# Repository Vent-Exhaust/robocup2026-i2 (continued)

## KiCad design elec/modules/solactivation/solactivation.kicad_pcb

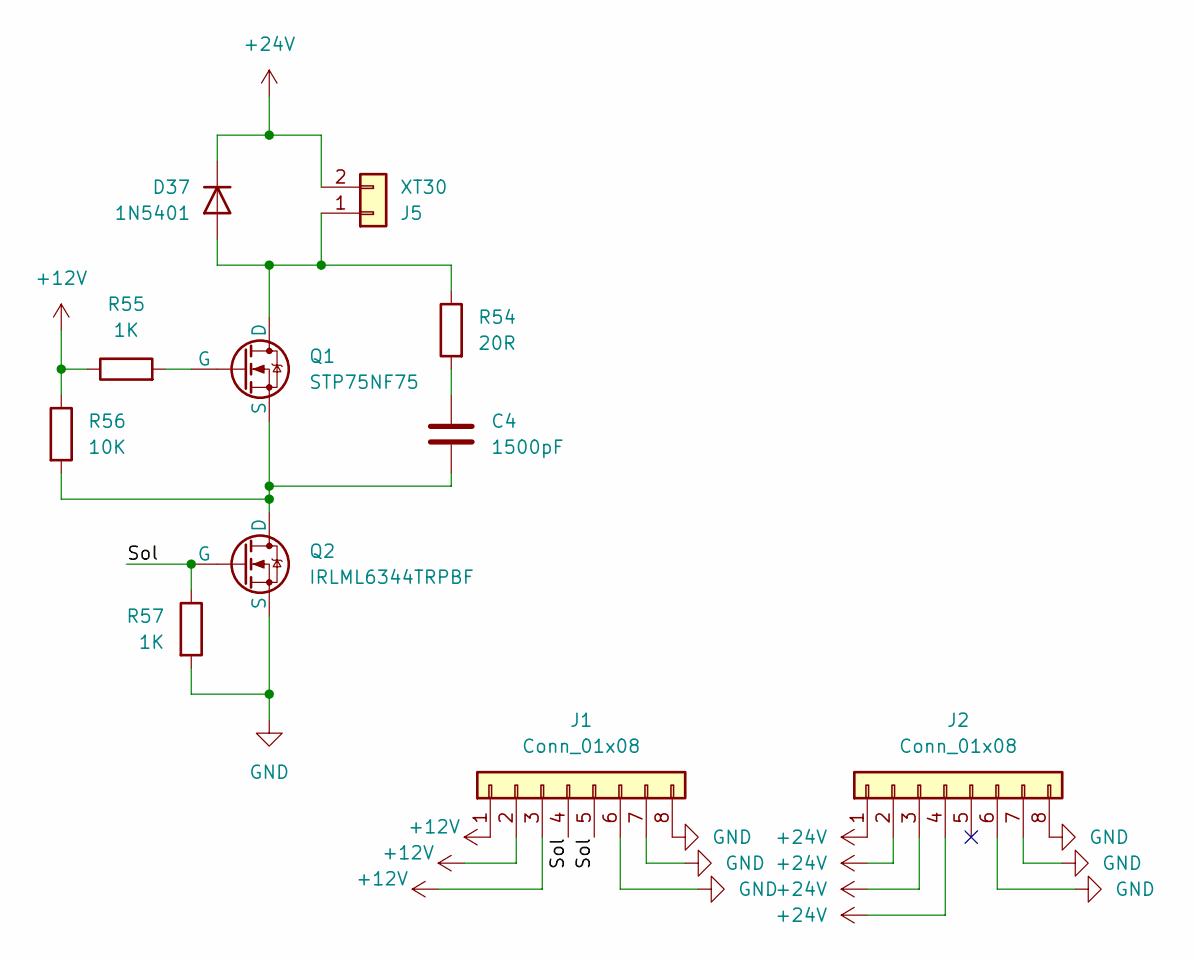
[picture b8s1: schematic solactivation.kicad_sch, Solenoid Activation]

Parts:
C4: 1500pF; cap0603; LCSC C107060
D37: 1N5401; D_DO-201AD_P15.24mm_Horizontal; LCSC C179506
J1, J2: Conn_01x08; PinSocket_1x08_P2.54mm_Vertical
J5: XT30; AMASS_XT30-F; LCSC C108769
Q1: STP75NF75; TO-220-3_Vertical; Mouser Part Number 726-IPD050N10N5ATMA1; LCSC C13678
Q2: IRLML6344TRPBF; SOT95P237X112-3N; Mouser Part Number 942-IRLML6344TRPBF
R54: 20R; res0603; LCSC C22950
R55, R57: 1K; res0603; LCSC C21190
R56: 10K; res0603; LCSC C25804

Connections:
+12V: J1.1, J1.2, J1.3, R55.1, R56.1
+24V: D37.1 (K), J2.1, J2.2, J2.3, J2.4, J5.2
/Sol: J1.4, J1.5, Q2.1 (G), R57.1
GND: J1.6, J1.7, J1.8, J2.6, J2.7, J2.8, Q2.2 (S), R57.2
unnamed: C4.1, R54.2
unnamed: D37.2 (A), J5.1, Q1.2 (D), R54.1
unnamed: Q1.1 (G), R55.2
unnamed: C4.2, Q1.3 (S), Q2.3 (D), R56.2

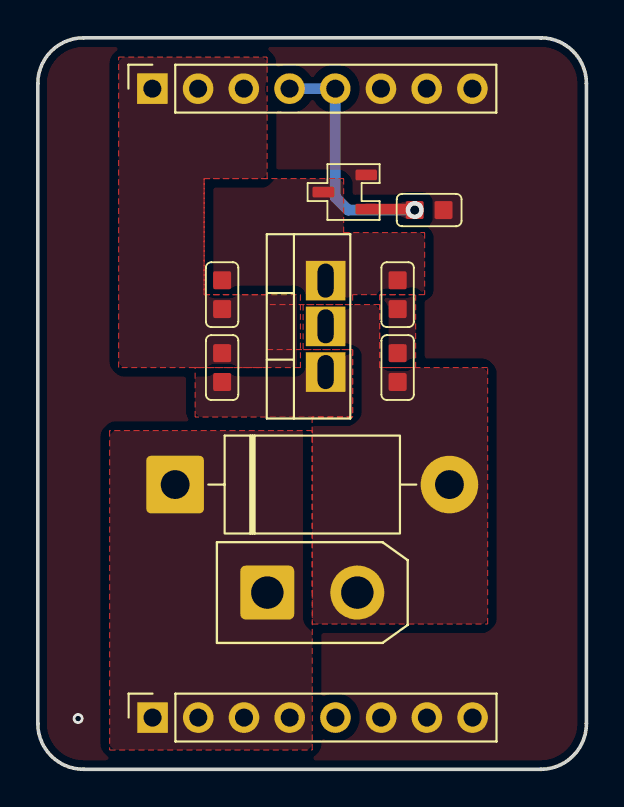
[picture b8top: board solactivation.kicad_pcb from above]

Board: 2 copper layers, 30.5 x 40.6 mm, 11 parts (0 on the bottom side), 8 nets.

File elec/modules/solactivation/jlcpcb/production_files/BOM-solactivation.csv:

Comment,Designator,Footprint,LCSC,Quantity
10K,R56,res0603,C25804,1
1500pF,C4,cap0603,C1595,1
1K,"R55,R57",res0603,C21190,2
20R,R54,res0603,C22950,1
IRLML6344TRPBF,Q2,SOT95P237X112-3N,,1

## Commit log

2025-10-08 added stuff
2025-10-14 did drivers yay
2025-10-14 did boost without caps for now might have to re config stitch vias pos
2025-10-14 fuction more impt!
2025-10-14 did motor driver example
2025-10-21 i think thats drivers done
2025-10-21 aligned pogos
2025-10-21 sleepy but did most pcbs
2025-10-21 updated modules dxfs
2025-10-21 motor drivers completed
2025-10-21 touched buck schematics
2025-10-22 added fusion fat module
2025-10-30 potentially did somethign
2025-10-31 moving somethings
2025-11-02 fix: edited buck
    moved a singular tantulum by a few mm
2025-11-02 did buck +3d models_ the actual buck er 3d mode'
2025-11-02 added TPS5430DDAG4 3d models
2025-11-03 finishe dcaps for boost
2025-11-03 did stuff
2025-11-03 forgot to close kicaed
2025-11-03 finished pcbs-silkscrfeen pcbs seem halal
2025-11-03 added teardrops and sus via
2025-11-03 added silkscreen
2025-11-05 did pcba for bucks
2025-11-05 did pcba for buck and boos5t
2025-11-30 added Bourns TC33X-2-104E
2025-11-30 feat: added pot to boost
2025-11-30 added 3d model for boost + PCBA
2025-11-30 Finished slaving avay buck done +PCBA
2025-11-30 added v1 to bucks
2025-11-30 added name cos why not
2025-12-02 chore: production files; chore: rev num for solactivation
2025-12-02 chore: boost production files
2025-12-02 chore: buck production files
2025-12-02 chore: boostcaps production files
2025-12-02 fix: boostcaps revision number; chore: boostcaps production files
2025-12-02 changed buck footprint
2025-12-10 feat: layer1-pcb-v1.0
2025-12-10 feat: cone mirror files
2025-12-10 partially did tofs
2026-01-02 Revert "Merge branch 'main' of https://github.com/2-chairs/robocup2026-i2"
    This reverts commit a28d608313404cc618c1ce11ffefa503b88e08b3, reversing
    changes made to 7cc45da3019f5272dff102d14f68ce9626e855f6.
2026-01-02 Revert "partially did tofs"
    This reverts commit 7cc45da3019f5272dff102d14f68ce9626e855f6.
2026-01-02 re buploaded tofs + kinda renamed and commited plagiarism
2026-01-03 made schematics more organised ish for tofs
    Hope i didnt mess anyuthingn up
2026-01-05 got l2 out of l2
2026-01-05 veryuseless change added dxf
2026-01-05 added light ring schematics
2026-01-05 closed kicad oops
2026-01-06 feat: light ring
2026-01-06 chore: update l1 dxf
2026-01-06 feat: layer1 light ring
2026-01-06 chore: stupid light ring more
2026-01-07 did l1 light ring partially
2026-01-07 done lightring
2026-01-07 added connectors for modules in schmatics
2026-01-07 mostly done with l1 scchematics
2026-01-08 fix: uploaded l1 2.0 dxf
2026-01-08 chore: src laser cutting files
2026-01-08 chore: wheels 3mf files
2026-01-08 chore: kicker 3mf files
2026-01-08 chore: dribbler 3mf files
2026-01-08 fix: dribbler 3mf files
2026-01-08 l1:added boost measurements
2026-01-08 feat: battery mount parts
2026-01-08 almost done maybe
2026-01-08 l1:connected most stuff
2026-01-08 fix: wheels cad
2026-01-08 styles: font
2026-01-08 fix: layer1 pcb
2026-01-09 feat: layer2 buck-module footprint and symbol
2026-01-09 feat: layer2 motor driver footprint and schematic
2026-01-09 feat: did something
2026-01-10 l1: added some stuff havent connected data to drivers yet
2026-01-10 connectred the pins for driver
2026-01-13 added lightgate kicad file
2026-01-13 added ldr folder
2026-01-13 did smth
2026-01-14 fixed light gate jst
2026-01-14 did some stuff on l2
2026-01-14 did something
2026-01-15 did smnth to l2
2026-01-15 FInished L2-l3 connection and branding
2026-01-16 stuff
2026-01-17 tofs:debranded it and added 1 via to add gnd fill
2026-01-17 did a bit of buck
2026-01-17 buck seems done idk
2026-01-17 driver jsts r almost done ig
2026-01-17 Revert "driver jsts r almost done ig"
    This reverts commit 0dd8e7197cd13faec0b768cbe0f6c1db0f8b679d.
2026-01-17 l2 domne
2026-01-18 l1 half motors done
2026-01-18 allah
2026-01-19 touched l1
2026-01-19 touched lit 1 thing on l2
2026-01-19 l1+l2 added jsts
2026-01-19 wdicajdfkj,
2026-01-19 b bmm mm
2026-01-19 Revert "b bmm mm"
    This reverts commit d7770a863270f1cb970ce90ee83eb730e8b22a2d.
2026-01-19 Revert "wdicajdfkj,"
    This reverts commit 449301836dc9eb174cafc9138a1f848e041cf83e.
2026-01-19 Revert "wdicajdfkj,"
    This reverts commit db7a6f9b2f59baf1fef59c53f0e0732f06b8b58b.
2026-01-19 Revert "wdicajdfkj,"
    This reverts commit e49fd520bb1bff58c9ec61a88596577cb6380b2a.
2026-01-19 Revert "buck seems done idk"
    This reverts commit 98c0c33bcc0f6ab69bf7f0e82d9e932e885d420a.
2026-01-19 Revert "did a bit of buck"
    This reverts commit f549f5fa1dabaa1ceabc4869307f1601dc61308a.
2026-01-19 unfucked bucks and touched on l1/2
2026-01-20 bucks done
2026-01-24 feat: cone mech files
2026-01-24 prod: l1 pcba prod
2026-01-24 prod: l1-l3
2026-01-24 prod: prod
2026-01-24 did pcba for tofs+increased dist between l1 to3 connection and sol activationi
2026-01-25 l2 : moved a singular via
2026-01-26 fix: minor issues
2026-01-26 moved 2 modules
2026-01-26 feat: stm32 module
2026-01-28 revelation: i quit
2026-01-28 fix: restart
2026-01-28 feat: l1 schematics
2026-01-28 feat: boost footprint
2026-01-29 chore: l1 mux routing
2026-01-29 feat: complete layer1
2026-01-29 docs: remark on phototransistors and photodiodes
2026-01-29 fix: l1 gnd
2026-01-29 fix: l1; chore: l2 schematics
2026-01-29 feat: l2 schematics
2026-01-30 feat: buck
2026-01-30 chore: delete l1.zip
2026-01-30 feat: buck.steps; chore: l2
2026-01-30 chore: l2
2026-01-30 feat: l2, lightgate
2026-01-30 finished rpouting +pcba
2026-01-30 did buck pcba
2026-02-02 l3: did schematics
2026-02-03 fix: l2
2026-02-03 l3 almost done
2026-02-03 l3 done
2026-02-04 l3: moved jsts
2026-02-04 l3 touched
2026-02-06 fix: l3
2026-02-06 l3 light touches
2026-02-07 prod: l2, l3
2026-02-07 l3 : edited schematics
2026-02-10 prod: cone
2026-02-11 l3: changed gpio pins for esp32 to avoid 2 and 9
2026-02-16 feat: cone
2026-02-16 feat: dribbler
2026-02-17 feat: mech: mirror
2026-02-18 fix: mech: ir shell
2026-02-20 added res and cap
2026-02-20 changed chenxuan mistake on l1
2026-02-20 feat: Binary converter
2026-02-23 feat: mech
2026-02-23 fix: mech: wheels
2026-02-23 fix: mech: dribbler mount
2026-02-23 l3 : sw change
2026-02-23 did l2 production files
2026-02-23 l1/3 production files updated
2026-02-25 feat: mux code
2026-02-25 did l1 add res partially
2026-02-25 feat: code: debug
2026-02-27 l1 done
2026-02-27 chore: code fix
2026-02-27 fix: l1; prod: l1
2026-02-27 fix: l1
2026-02-28 l3 : done
2026-02-28 l1 pcba
2026-02-28 light touches on l2
2026-02-28 fixed enable pull dowj
2026-02-28 chore: translucency test
2026-02-28 feat: mech: lightringshell
2026-02-28 chore: mech: lightring
2026-03-01 chore: mech: lightring shell
2026-03-01 chore: mech: fix lightring shell
2026-03-01 l3 light touvh
2026-03-01 l2 done
2026-03-01 chore: cleanup layer1 pcb
2026-03-01 all layes drc and fixed
2026-03-02 chore: fix all 3 layers; prod: all 3 layers
2026-03-03 fix: fix code to take average instead
2026-03-03 refactor: restructure entire code folder
2026-03-03 docs: update readme
2026-03-03 chore: fix docs typo
2026-03-04 chore: fix typo in readme
2026-03-06 feat: cam code
2026-03-10 feat: fix cam code
2026-03-10 chore: turn off debug
2026-03-10 chore: debug for cross
2026-03-10 chore: fix folder name
2026-03-10 chore: mech: fix top layers
2026-03-10 docs: upload media
2026-03-12 feat: mech: handle, cam shroud, dribbler mould
2026-03-12 feat: l3 espnow test code
2026-03-12 feat: l2 init code, fix
2026-03-12 fix: l1 platformio init
2026-03-12 fix: l2 init code
2026-03-14 chore: media
2026-03-14 chore: l2 code for testing
2026-03-14 chore: mech: updated dribbler drum
2026-03-14 chore: rearrange files
2026-03-14 chore: mech: reorganise files
2026-03-16 feat: mech: dribbler fixes, kicker fixes
2026-03-18 chore: mech: alot of stuff
2026-03-18 chore: code: alot of stuff
2026-03-18 feat: code alot
2026-03-18 fix: remap angles
2026-03-18 feat: code
2026-03-19 feat: code: imu
2026-03-19 chore: mech: update wheels files
2026-03-19 feat: alot of movement
2026-03-20 chore: mech: fix dribbler
2026-03-20 refactor: entire code base reorganised
2026-03-20 chore: cam regression
2026-03-20 chore: mech: rollers print file
2026-03-20 feat: major movement code fixes and improvements
2026-03-20 chore: movement tuning and algorithom fixes
2026-03-21 feat: cam regression and transmission
2026-03-21 feat: l2 receive cam data
2026-03-21 chore: mirror polynomial graph
2026-03-21 chore: clean up layer2 code
2026-03-21 chore: layer3 ir detect ball heading and size
    yet to test
2026-03-21 chore: fix ir code to use num of ir not num of counts
2026-03-21 chore: fix ir detection, change ir calculation
2026-03-21 chore: update layer2 main.h
2026-03-22 chore: cut weight
2026-03-27 chore: tune for home
2026-03-27 chore: go to ball code
2026-03-27 chore: motor test code
2026-03-27 chore: mech print files
2026-03-27 chore: fix offset
2026-03-27 chore: fix regression
2026-03-27 chore: update cam regression graph
2026-03-27 chore: random cam code stuff
2026-03-27 fix: fix moveRobot code, program move to ball
2026-03-28 chore: update mech print files
2026-03-28 chore: update cam code
2026-03-28 chore: tune for cx home
2026-03-28 feat: go to ball, go to center, localisation and others
2026-03-31 chore: update mech files
2026-03-31 chore: cam, l2 score
2026-03-31 chore: checkCatchment function
2026-04-01 chore: update dribbler print files
2026-04-01 chore: CLAUDE.md
2026-04-05 chore: add dribbler debug code
2026-04-06 feat: orbit, tuning
2026-04-06 chore: bang-bang control loop for orbit
2026-04-06 chore: kp control loop for orbit
2026-04-06 chore: creep forward when aligned
2026-04-06 feat: scoring!!!
2026-04-06 chore: bot 2 config
2026-04-07 tried and failed goalie
2026-04-07 did some code in theory
2026-04-07 "referenced " ducc code and made deadzone variable
2026-04-08 added ducc math
2026-04-08 hkbecwd
    jkhA
2026-04-08 omds idk what im doing anymore
2026-04-09 chore: socks strat
2026-04-09 chore: score
2026-04-09 feat: scoring
2026-04-09 i givbeb up
2026-04-09 chore: yellow goal
2026-04-09 chore: goalie
2026-04-10 feat: goalie localisation curve
2026-04-10 feat: goalie
2026-04-10 chore: move config.h variables to top
2026-04-10 chore: kicker plate
2026-04-10 fix: yellow goalie
2026-04-10 chore: idk line avoidance or somethig
2026-04-10 chore: tune?
2026-04-10 feat: basic tuning
2026-04-10 chore: goal rush
2026-04-10 chore: update mech
2026-04-10 chore: update pinhole
2026-04-11 chore: tuning
2026-04-11 chore: slight tuning
2026-04-12 chore: tune config.h
2026-04-18 feat: final code configs, update code README.md
2026-05-06 Update README docs
2026-05-06 Add README photo gallery
2026-05-06 Document media directory in README
2026-05-06 Correct camera documentation
2026-05-06 Update README gallery formatting
2026-05-06 Increase README gallery preview resolution
2026-05-09 fixed l1 sw
2026-05-09 did stuff ( uncursed stupid cx vias )
